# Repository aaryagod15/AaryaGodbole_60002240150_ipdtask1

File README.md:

IPD Task01- AVR Microcontroller Board
Name - Aarya Godbole
Roll no - E137
SAP id - 60002240150
Div / Batch - E3 / 1

#repo stucture
- hardware : contains schematic and pcb layout.
- fabrication : has the gerber and drill files.
- datasheets : contains datasheets of the components.

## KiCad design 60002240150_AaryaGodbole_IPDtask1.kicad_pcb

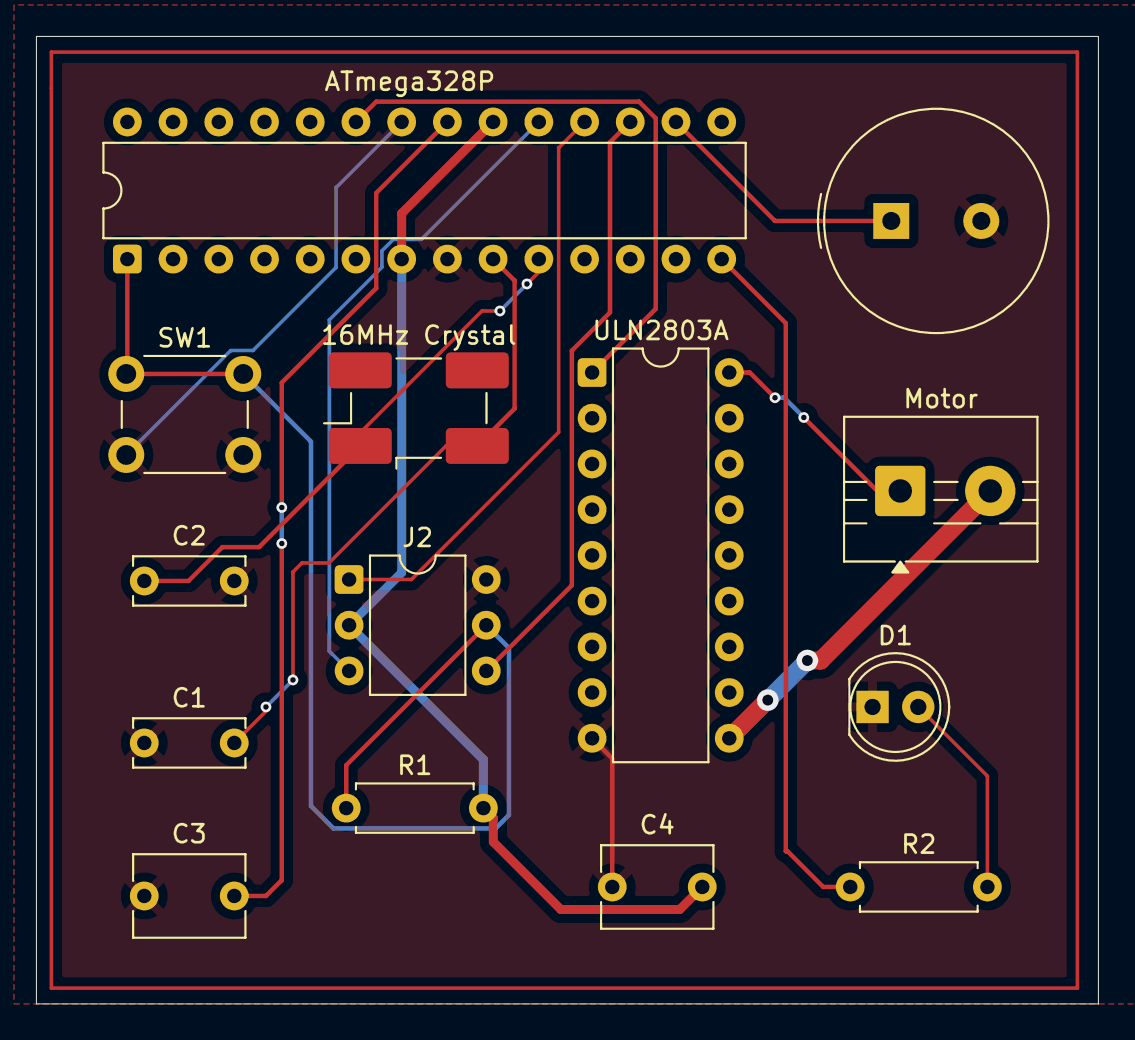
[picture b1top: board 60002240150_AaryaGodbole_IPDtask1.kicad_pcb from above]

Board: 2 copper layers, 59.0 x 53.8 mm, 14 parts (0 on the bottom side), 15 nets.

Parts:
16MHz Crystal: 16MHz; Oscillator_SMD_EuroQuartz_XO91-4Pin_7.0x5.0mm_HandSoldering
ATmega328P: ATmega328P-P; DIP-28_W7.62mm
BZ1: Buzzer; Buzzer_TDK_PS1240P02BT_D12.2mm_H6.5mm
C1, C2: 22p; C_Disc_D6.0mm_W2.5mm_P5.00mm
C3, C4: 100n; C_Disc_D6.0mm_W4.4mm_P5.00mm
D1: LED; LED_D5.0mm
J2: AVR-ISP-6; DIP-6_W7.62mm
Motor: Conn_01x02_Pin; TerminalBlock_MaiXu_MX126-5.0-02P_1x02_P5.00mm
R1: 10k; R_Axial_DIN0207_L6.3mm_D2.5mm_P7.62mm_Horizontal
R2: 220; R_Axial_DIN0207_L6.3mm_D2.5mm_P7.62mm_Horizontal
SW1: SW_Push; SW_PUSH_6mm
ULN2803A: ULN2803A; DIP-18_W7.62mm

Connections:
+5V: ATmega328P.7 (VCC), ATmega328P.20 (AVCC), C4.2, J2.2 (VCC), R1.2
+12V: Motor.2, ULN2803A.10 (COM)
GND: ATmega328P.8 (GND), ATmega328P.22 (GND), BZ1.2 (-), C1.1, C2.2, C3.1, C4.1, D1.1 (K), J2.6 (GND), SW1.2, ULN2803A.9 (GND)
unnamed: ATmega328P.16 (PB2), BZ1.1 (+)
unnamed: D1.2 (A), R2.2
unnamed: Motor.1, ULN2803A.18 (O1)
unnamed: ATmega328P.18 (PB4), J2.1 (MISO)
unnamed: ATmega328P.17 (PB3), J2.4 (MOSI)
unnamed: ATmega328P.19 (PB5), J2.3 (SCK)
unnamed: ATmega328P.1 (~RESET/PC6), J2.5 (~RST), R1.1, SW1.1
unnamed: ATmega328P.21 (AREF), C3.2
unnamed: ATmega328P.14 (PB0), R2.1
unnamed: ATmega328P.23 (PC0), ULN2803A.1 (I1)
unnamed: 16MHz Crystal.2, ATmega328P.9 (XTAL1/PB6), C1.2
unnamed: 16MHz Crystal.1, ATmega328P.10 (XTAL2/PB7), C2.1

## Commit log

2026-03-01 Add files via upload
    Final submission
2026-03-01 Create Temp
